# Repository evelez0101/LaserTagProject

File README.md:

# LaserTagProject
Common Project for Art of Eng. @ Columbia

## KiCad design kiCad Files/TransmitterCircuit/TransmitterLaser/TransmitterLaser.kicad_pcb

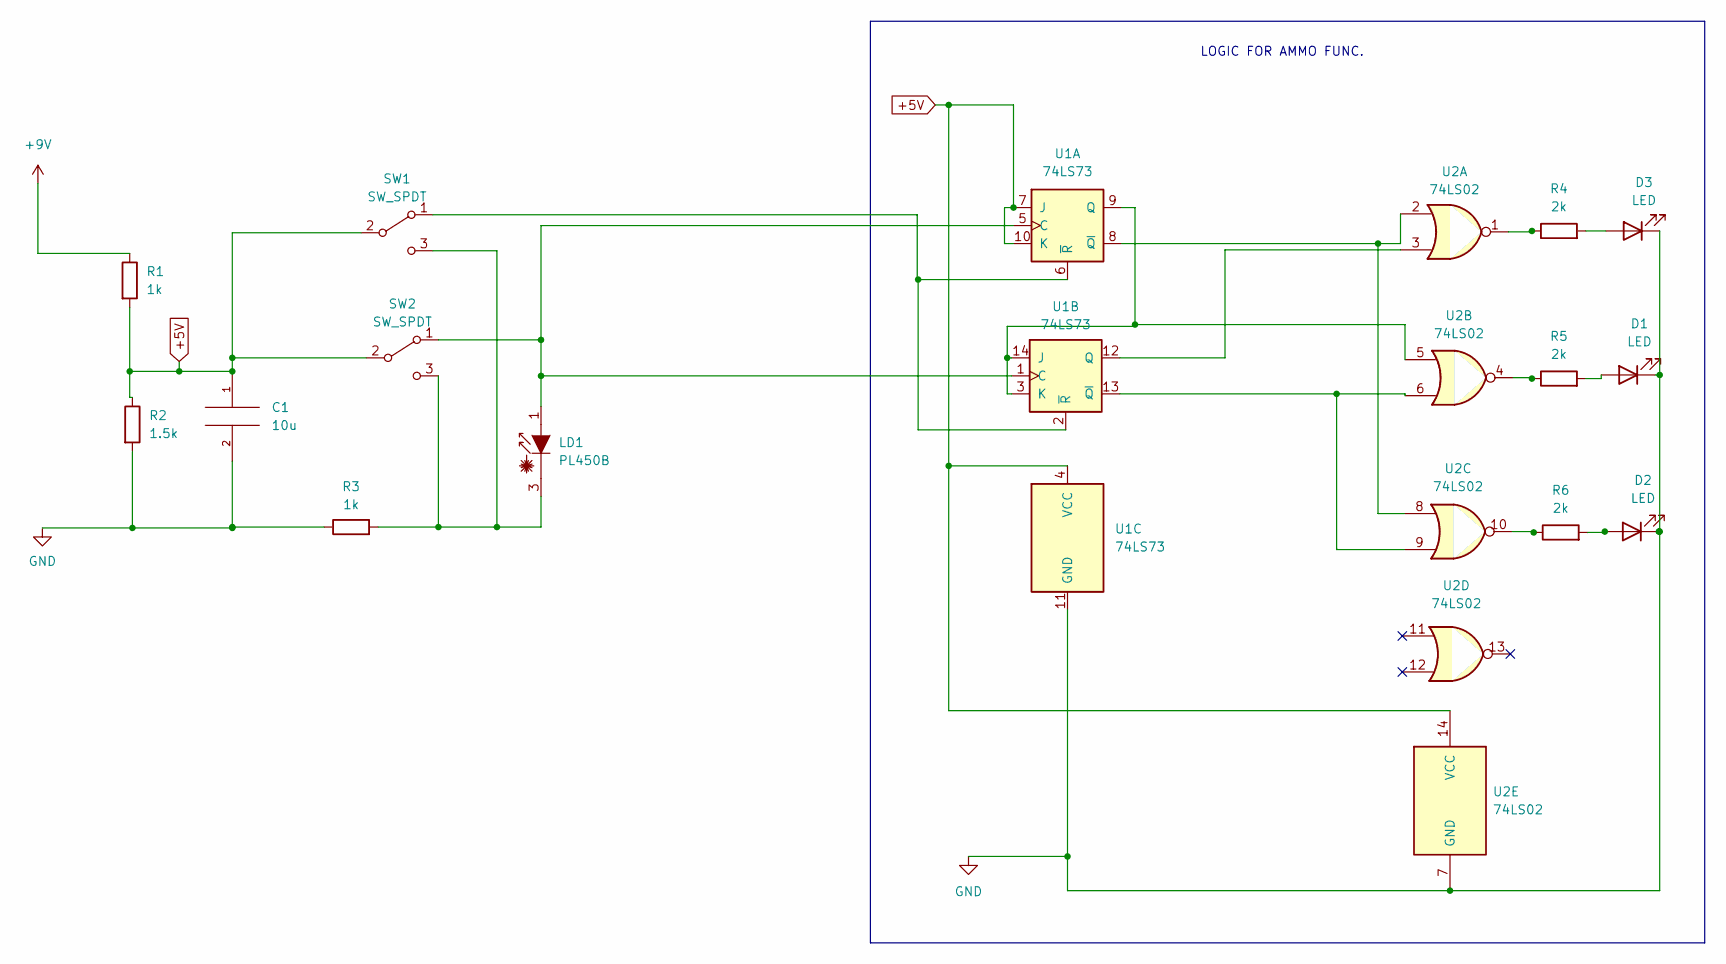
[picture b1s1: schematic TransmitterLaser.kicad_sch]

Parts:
C1: 10u; CP_Radial_D4.0mm_P1.50mm
D1, D2, D3: LED; LED_D3.0mm
LD1: PL450B; LaserDiode_TO38ICut-3
R1, R3: 1k; R_Axial_DIN0204_L3.6mm_D1.6mm_P7.62mm_Horizontal
R2: 1.5k; R_Axial_DIN0204_L3.6mm_D1.6mm_P7.62mm_Horizontal
R4, R5, R6: 2k; R_Axial_DIN0204_L3.6mm_D1.6mm_P7.62mm_Horizontal
SW1, SW2: SW_SPDT; PinHeader_1x03_P1.27mm_Vertical
U1: 74LS73; DIP-14_W7.62mm
U2: 74LS02; DIP-14_W7.62mm

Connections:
+5V: C1.1, R1.2, R2.1, SW1.2 (B), SW2.2 (B), U1.4 (VCC), U1.7 (J), U1.10 (K), U2.14 (VCC)
+9V: R1.1
GND: C1.2, D1.1 (K), D2.1 (K), D3.1 (K), R2.2, R3.1, U1.11 (GND), U2.7 (GND)
unnamed: D1.2 (A), R5.2
unnamed: D2.2 (A), R6.2
unnamed: D3.2 (A), R4.2
unnamed: LD1.1 (A), SW2.1 (A), U1.1 (C), U1.5 (C)
unnamed: LD1.3 (C), R3.2, SW1.3 (C), SW2.3 (C)
unnamed: R4.1, U2.1
unnamed: R5.1, U2.4
unnamed: R6.1, U2.10
unnamed: SW1.1 (A), U1.2 (~R), U1.6 (~R)
unnamed: U1.8 (~Q), U2.2, U2.8
unnamed: U1.12 (Q), U2.3
unnamed: U1.13 (~Q), U2.6, U2.9
unnamed: U1.3 (K), U1.9 (Q), U1.14 (J), U2.5

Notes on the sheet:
LOGIC FOR AMMO FUNC.

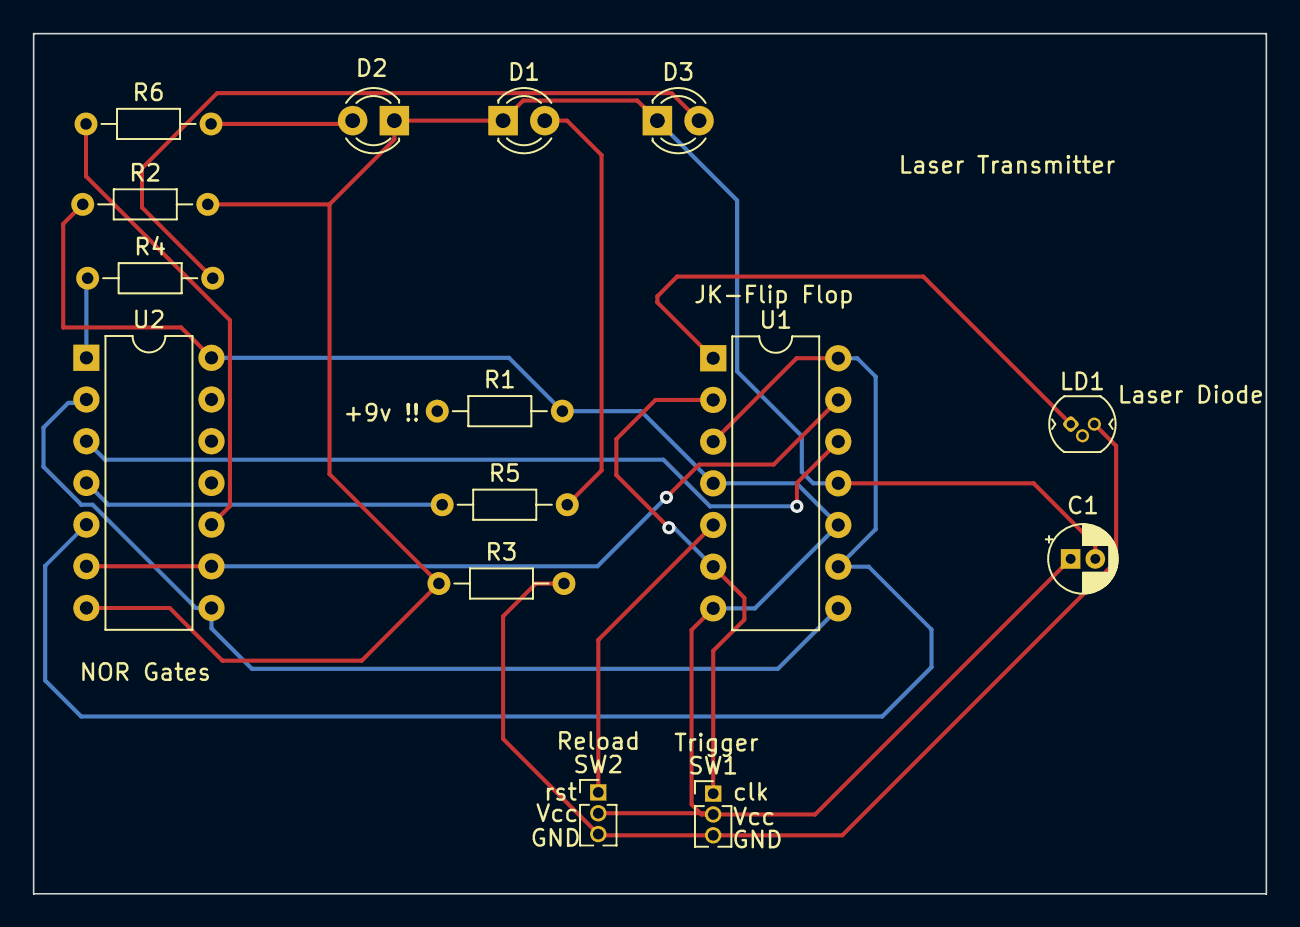
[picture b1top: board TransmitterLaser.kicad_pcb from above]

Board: 2 copper layers, 75.1 x 52.4 mm, 15 parts (0 on the bottom side), 15 nets.

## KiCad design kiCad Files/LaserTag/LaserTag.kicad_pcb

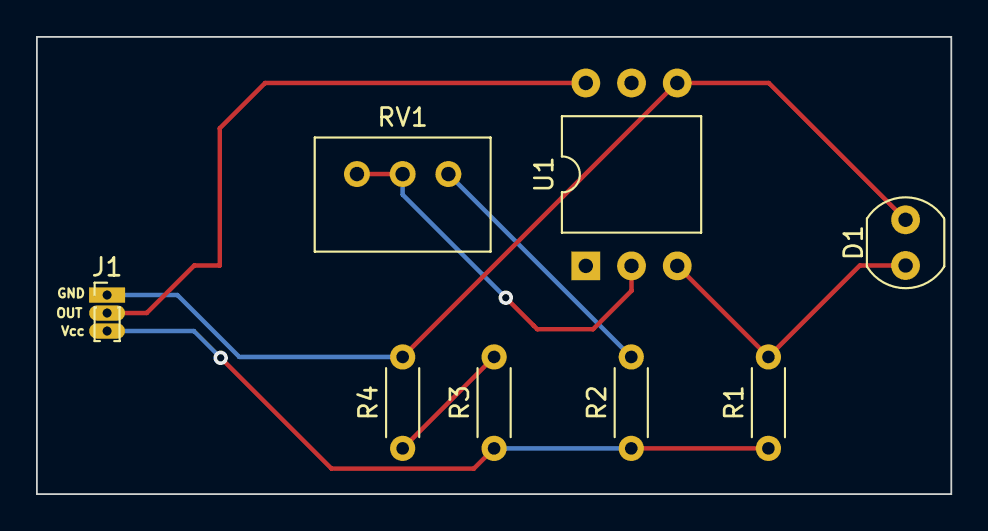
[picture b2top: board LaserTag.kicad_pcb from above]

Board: 2 copper layers, 50.8 x 25.4 mm, 8 parts (0 on the bottom side), 7 nets.

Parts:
D1: D_Photo_Filled; R_LDR_4.9x4.2mm_P2.54mm_Vertical
J1: Conn_01x03; PinHeader_1x03_P1.00mm_Vertical
R1, R2: R_US; R_Axial_DIN0204_L3.6mm_D1.6mm_P5.08mm_Horizontal
R3: 10k; R_Axial_DIN0204_L3.6mm_D1.6mm_P5.08mm_Horizontal
R4: 20k; R_Axial_DIN0204_L3.6mm_D1.6mm_P5.08mm_Horizontal
RV1: R_Potentiometer; Potentiometer_Bourns_3299W_Vertical
U1: LM741; DIP-6_W10.16mm

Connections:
+5v: R3.2, R4.1
+9V: J1.3, R1.1, R2.1, R3.1
GND: D1.2 (A), J1.1, R4.2, U1.4 (V-)
unnamed: D1.1 (K), R1.2, U1.3 (+)
unnamed: R2.2, RV1.1
unnamed: RV1.2, RV1.3, U1.2 (-)
unnamed: J1.2, U1.6

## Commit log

2023-02-09 initialized file structures
2023-02-09 Create Arduino
2023-02-09 restructured file system
2023-02-11 aspheric lens idea
2023-02-11 laser receiver + transmitter circuit v1
2023-02-11 schematic + pcb + 3d model made
2023-02-26 transmitter Circuit created + receiver resized
2023-04-12 Update and rename software_V1.0 to software_V2
2023-04-12 Create Sensor_Processing
2023-04-12 Rename Sensor_Processing to Sensor_Processing.ino
2023-04-12 Rename software_V2 to software_V2.ino
2023-04-24 test code for new receiver
2023-04-25 creds to schematic
